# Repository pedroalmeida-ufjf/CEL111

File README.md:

# CEL111
Laboratório de Prototipagem Eletrônica

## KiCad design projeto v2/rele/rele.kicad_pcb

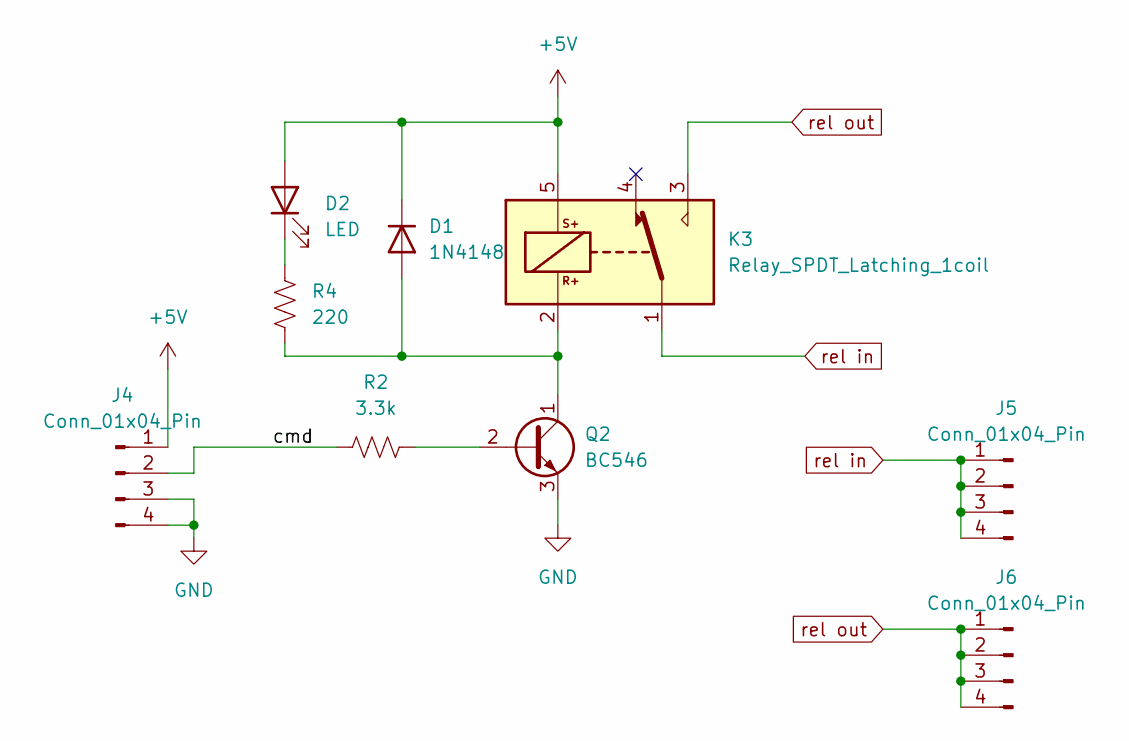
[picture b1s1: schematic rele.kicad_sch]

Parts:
D1: 1N4148; D_DO-35_SOD27_P7.62mm_Horizontal
D2: LED; LED_D3.0mm_Clear
J4, J5, J6: Conn_01x04_Pin; PinHeader_1x04_P2.54mm_Vertical
K3: Relay_SPDT_Latching_1coil; Relay_SPDT_SANYOU_SRD_Series_Form_C
Q2: BC546; TSOT-23
R2: 3.3k; R_0805_2012Metric
R4: 220; R_0805_2012Metric

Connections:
+5V: D1.1 (K), D2.2 (A), J4.1, K3.5
/cmd: J4.2, R2.2
GND: J4.3, J4.4, Q2.3 (E)
unnamed: D1.2 (A), K3.2, Q2.1 (C), R4.1
unnamed: D2.1 (K), R4.2
unnamed: Q2.2 (B), R2.1
rel in: J5.1, J5.2, J5.3, J5.4, K3.1
rel out: J6.1, J6.2, J6.3, J6.4, K3.3

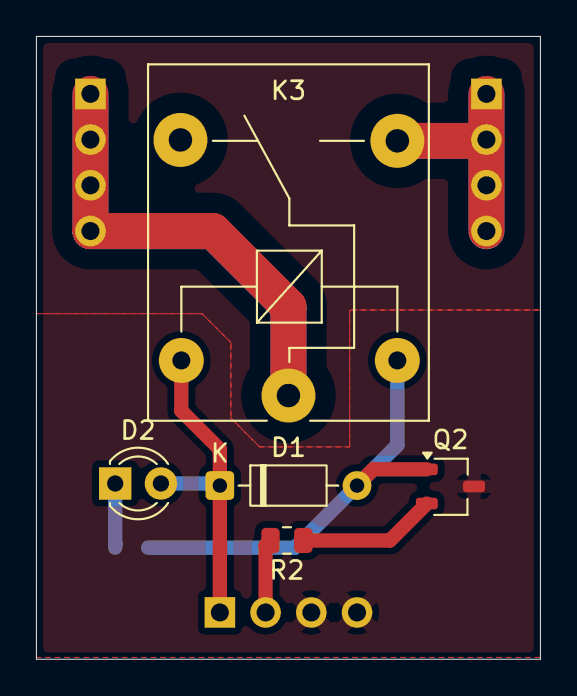
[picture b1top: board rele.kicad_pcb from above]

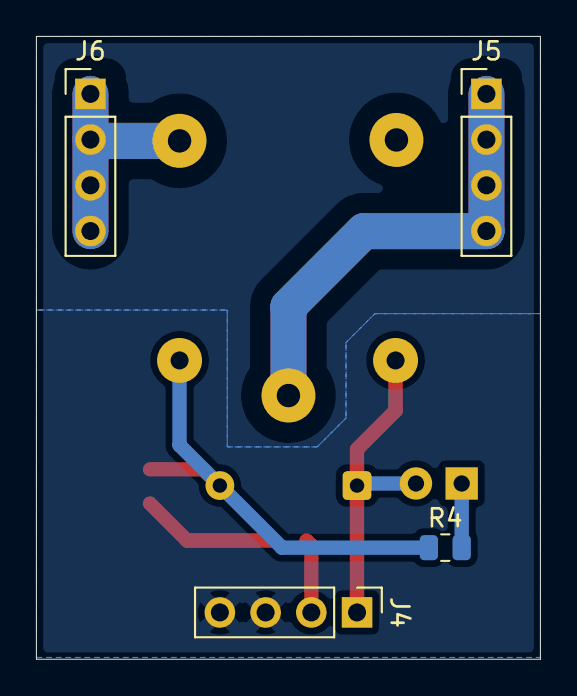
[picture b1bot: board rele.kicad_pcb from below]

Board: 2 copper layers, 28.0 x 34.6 mm, 9 parts (4 on the bottom side), 8 nets.

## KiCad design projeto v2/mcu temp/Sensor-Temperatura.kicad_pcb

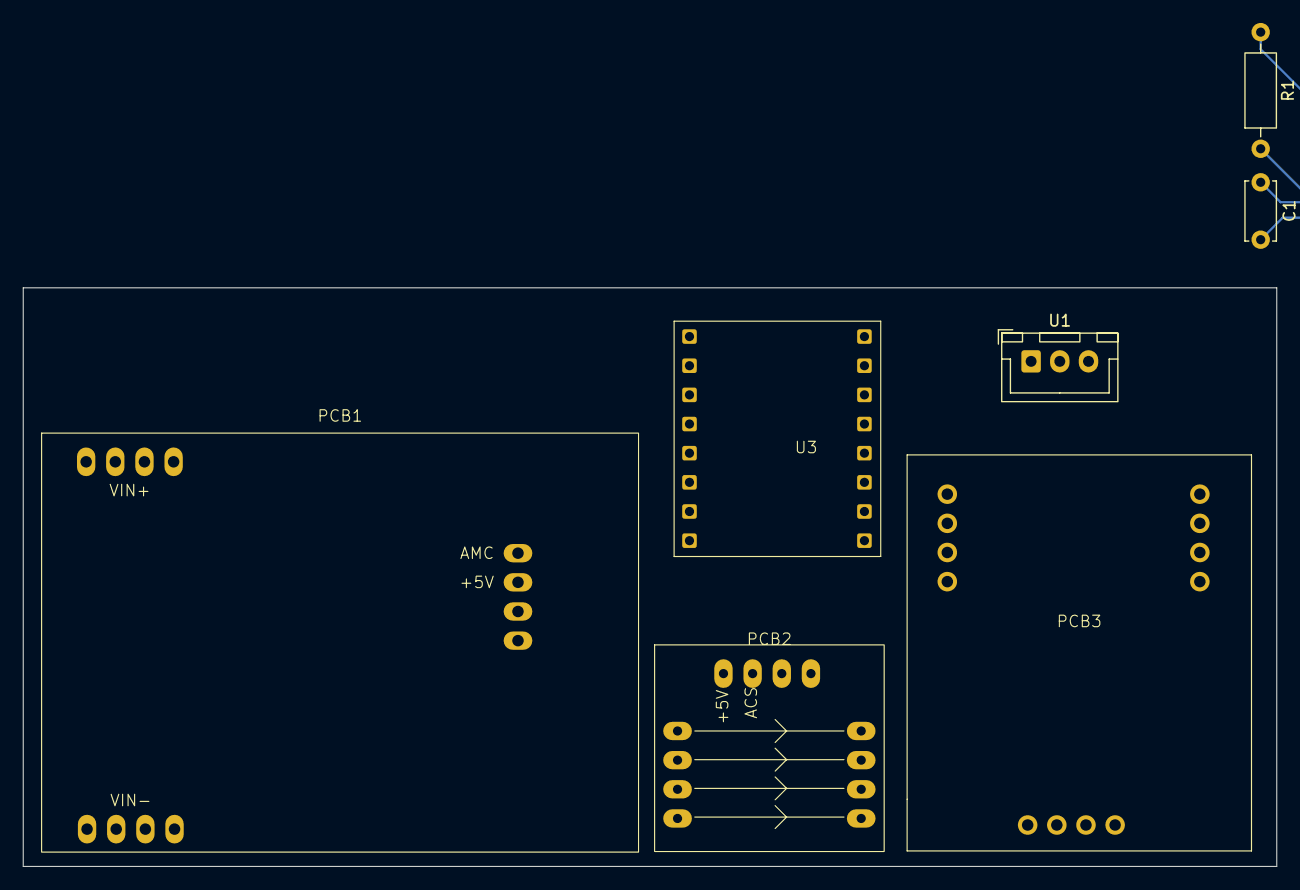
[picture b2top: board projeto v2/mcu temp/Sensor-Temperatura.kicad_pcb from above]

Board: 2 copper layers, 109.2 x 50.4 mm, 7 parts (0 on the bottom side), 9 nets.

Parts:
C1: 100nF; C_Disc_D5.0mm_W2.5mm_P5.00mm
PCB1: V-SENS
PCB2: I-SENS
PCB3: rele
R1: 4.7k; R_Axial_DIN0207_L6.3mm_D2.5mm_P10.16mm_Horizontal
U1: DS18B20; JST_XH_B3B-XH-A_1x03_P2.50mm_Vertical
U3: ESP32-C3_SUPERMINI_SMD; ESP32_C3_Supermini

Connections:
+3.3V: C1.1, R1.1, U1.3 (V_{DD}), U3.3.3 (3V3)
+5V: PCB1.10 (+5V), PCB2.9 (+5V), PCB3.10 (+5V), U3.5V
/TEMP_1WIRE: R1.2, U1.2 (DQ), U3.6 (GPIO6)
/VIN+: PCB1.1 (+VIN1), PCB1.2 (+VIN2), PCB1.3 (+VIN2), PCB1.4 (+VIN4), PCB2.1 (+IP), PCB2.2 (+IP), PCB2.3 (+IP), PCB2.4 (+IP)
/VIN-: PCB1.5 (-VIN1), PCB1.6 (-VIN2), PCB1.7 (-VIN2), PCB1.8 (-VIN4)
CMD: PCB3.9 (CMD), U3.3 (GPIO3)
GND: C1.2, PCB1.11 (GND), PCB1.12 (GND), PCB2.11 (GND), PCB2.12 (GND), PCB3.11 (GND), PCB3.12 (GND), U1.1 (GND), U3.G (GND)
unnamed: PCB3.5 (RLY-OUT), PCB3.6 (RLY-OUT), PCB3.7 (RLY-OUT), PCB3.8 (RLY-OUT)
unnamed: PCB2.5 (-IP), PCB2.6 (-IP), PCB2.7 (-IP), PCB2.8 (-IP), PCB3.1 (RLY-IN), PCB3.2 (RLY-IN), PCB3.3 (RLY-IN), PCB3.4 (RLY-IN)

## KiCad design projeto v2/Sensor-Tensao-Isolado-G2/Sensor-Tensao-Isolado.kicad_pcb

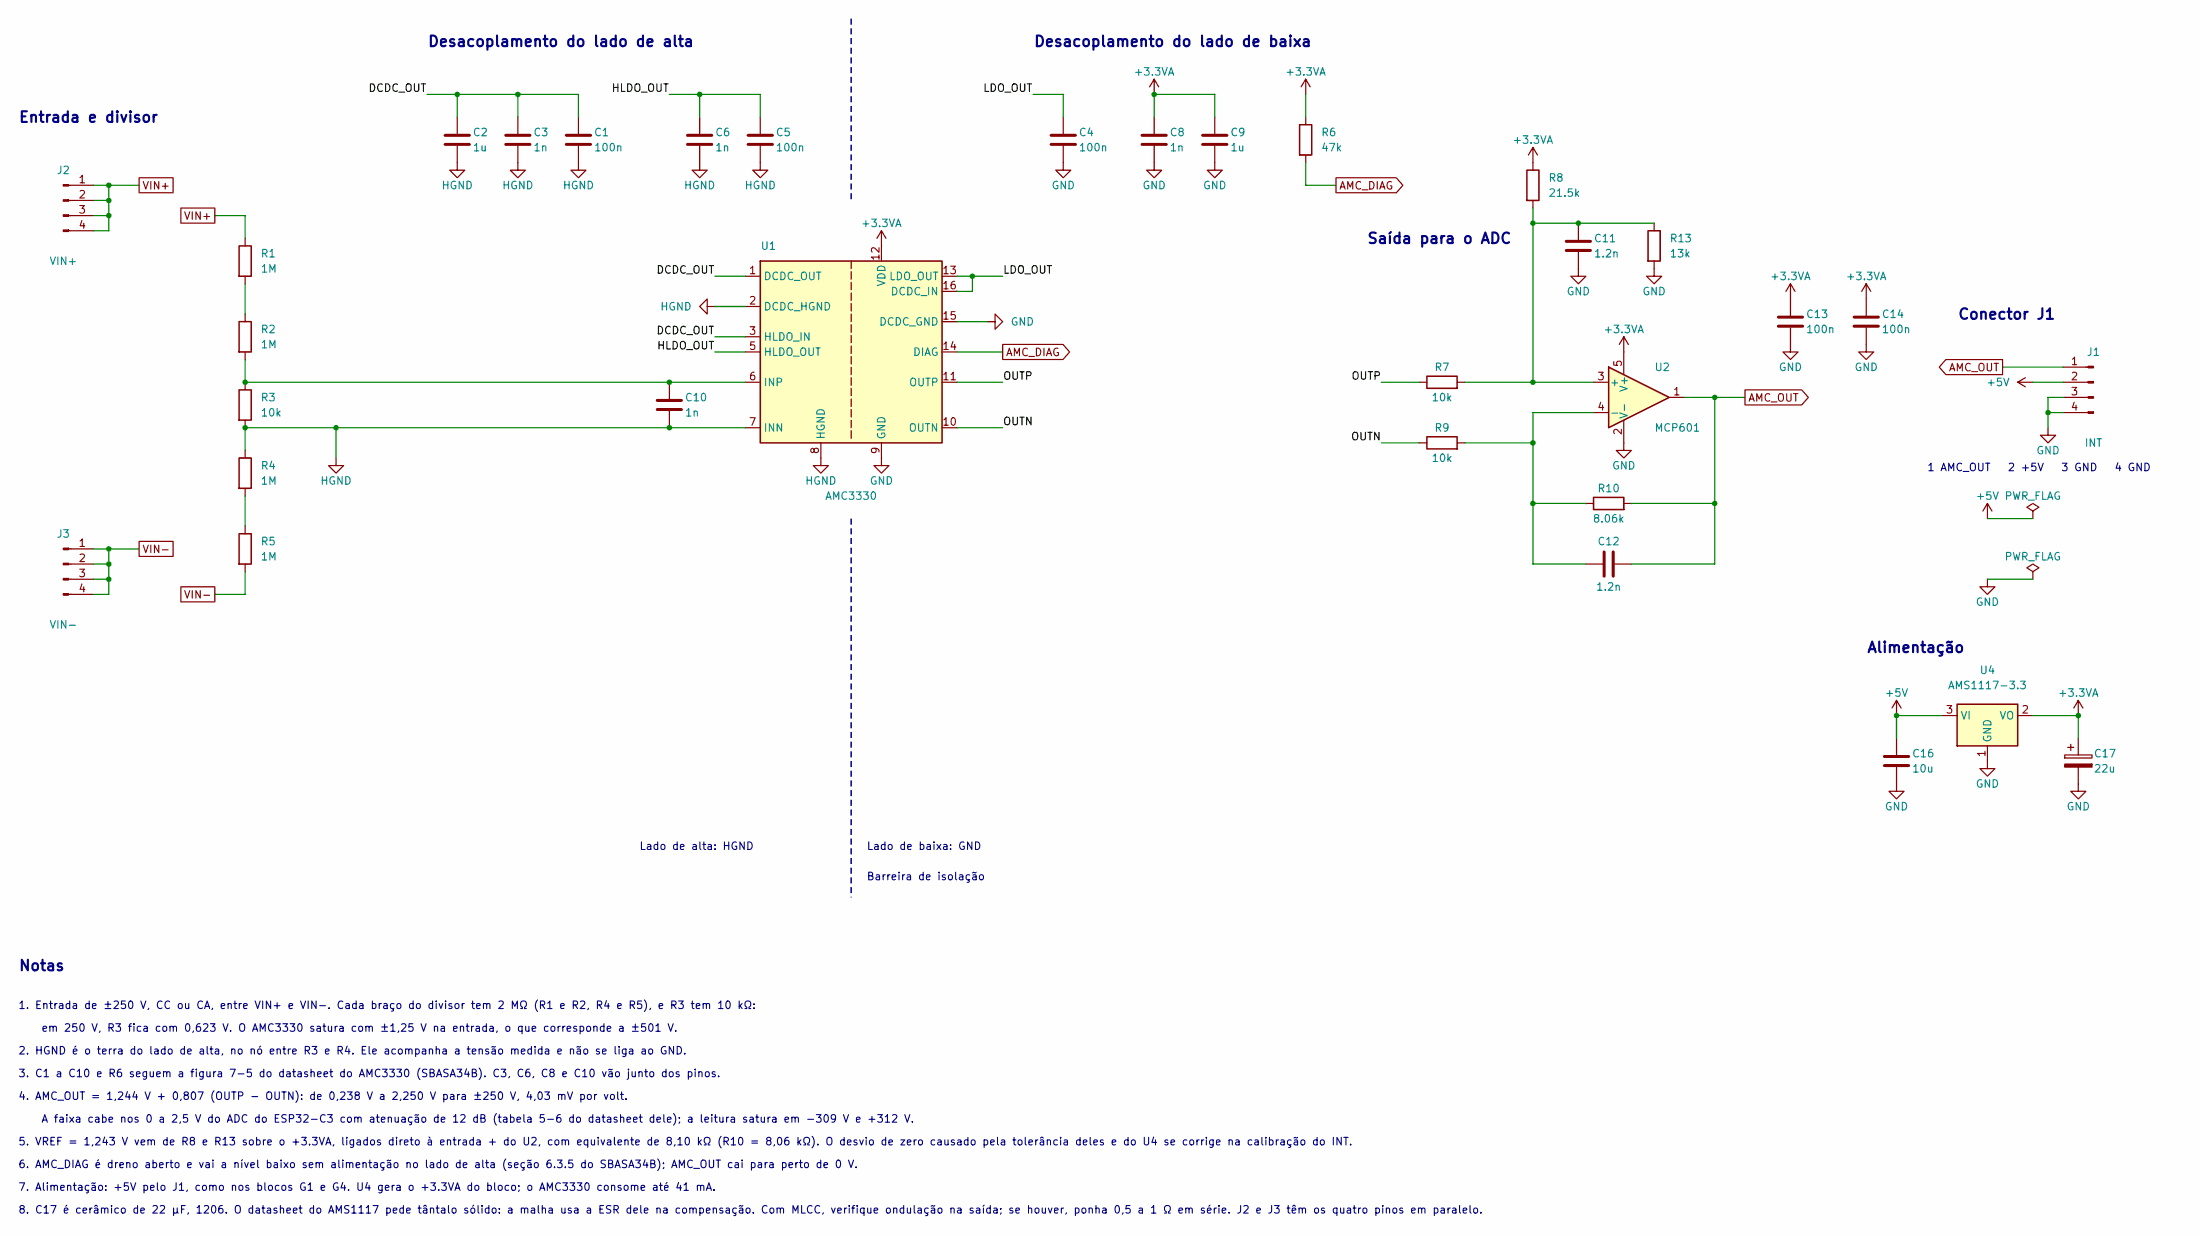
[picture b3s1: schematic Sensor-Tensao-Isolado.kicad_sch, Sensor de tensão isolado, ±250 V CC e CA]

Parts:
C1, C4, C5, C13, C14: 100n; C_1206_3216Metric_Pad1.33x1.80mm_HandSolder
C2, C9: 1u; C_1206_3216Metric_Pad1.33x1.80mm_HandSolder
C3, C6, C8, C10: 1n; C_1206_3216Metric_Pad1.33x1.80mm_HandSolder
C11, C12: 1.2n; C_1206_3216Metric_Pad1.33x1.80mm_HandSolder
C16: 10u; C_1206_3216Metric_Pad1.33x1.80mm_HandSolder
C17: 22u; C_1206_3216Metric_Pad1.33x1.80mm_HandSolder
J1: INT; PinHeader_1x04_P2.54mm_Vertical
J2: VIN+; PinHeader_1x04_P2.54mm_Vertical
J3: VIN-; PinHeader_1x04_P2.54mm_Vertical
R1, R2, R4, R5: 1M; R_1206_3216Metric_Pad1.30x1.75mm_HandSolder
R3, R7, R9: 10k; R_1206_3216Metric_Pad1.30x1.75mm_HandSolder
R6: 47k; R_1206_3216Metric_Pad1.30x1.75mm_HandSolder
R8: 21.5k; R_1206_3216Metric_Pad1.30x1.75mm_HandSolder
R10: 8.06k; R_1206_3216Metric_Pad1.30x1.75mm_HandSolder
R13: 13k; R_1206_3216Metric_Pad1.30x1.75mm_HandSolder
U1: AMC3330; SOIC-16W_7.5x10.3mm_P1.27mm
U2: MCP601; SOT-23-5
U4: AMS1117-3.3; SOT-223-3_TabPin2

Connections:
+3.3VA: C8.1, C9.1, C13.1, C14.1, C17.1, R6.1, R8.1, U1.12 (VDD), U2.5 (V+), U4.2 (VO)
+5V: C16.1, J1.2, U4.3 (VI)
/DCDC_OUT: C1.1, C2.1, C3.1, U1.1 (DCDC_OUT), U1.3 (HLDO_IN)
/HLDO_OUT: C5.1, C6.1, U1.5 (HLDO_OUT)
/LDO_OUT: C4.1, U1.13 (LDO_OUT), U1.16 (DCDC_IN)
/OUTN: R9.1, U1.10 (OUTN)
/OUTP: R7.1, U1.11 (OUTP)
AMC_DIAG: R6.2, U1.14 (DIAG)
AMC_OUT: C12.2, J1.1, R10.2, U2.1
GND: C4.2, C8.2, C9.2, C11.2, C13.2, C14.2, C16.2, C17.2, J1.3, J1.4, R13.2, U1.9 (GND), U1.15 (DCDC_GND), U2.2 (V-), U4.1 (GND)
HGND: C1.2, C2.2, C3.2, C5.2, C6.2, C10.2, R3.2, R4.1, U1.2 (DCDC_HGND), U1.7 (INN), U1.8 (HGND)
unnamed: R1.2, R2.1
unnamed: R4.2, R5.1
unnamed: C10.1, R2.2, R3.1, U1.6 (INP)
unnamed: C11.1, R7.2, R8.2, R13.1, U2.3 (+)
unnamed: C12.1, R9.2, R10.1, U2.4 (-)
VIN+: J2.1, J2.2, J2.3, J2.4, R1.1
VIN-: J3.1, J3.2, J3.3, J3.4, R5.2

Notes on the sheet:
8. C17 é cerâmico de 22 µF, 1206. O datasheet do AMS1117 pede tântalo sólido: a malha usa a ESR dele na compensação. Com MLCC, verifique ondulação na saída; se houver, ponha 0,5 a 1 Ω em série. J2 e J3 têm os quatro pinos em paralelo.
em 250 V, R3 fica com 0,623 V. O AMC3330 satura com ±1,25 V na entrada, o que corresponde a ±501 V.
Lado de baixa: GND
1 AMC_OUT 2 +5V 3 GND 4 GND
Barreira de isolação
7. Alimentação: +5V pelo J1, como nos blocos G1 e G4. U4 gera o +3.3VA do bloco; o AMC3330 consome até 41 mA.
Lado de alta: HGND
4. AMC_OUT = 1,244 V + 0,807 (OUTP - OUTN): de 0,238 V a 2,250 V para ±250 V, 4,03 mV por volt.
Notas
1. Entrada de ±250 V, CC ou CA, entre VIN+ e VIN-. Cada braço do divisor tem 2 MΩ (R1 e R2, R4 e R5), e R3 tem 10 kΩ:
Entrada e divisor
6. AMC_DIAG é dreno aberto e vai a nível baixo sem alimentação no lado de alta (seção 6.3.5 do SBASA34B); AMC_OUT cai para perto de 0 V.
3. C1 a C10 e R6 seguem a figura 7-5 do datasheet do AMC3330 (SBASA34B). C3, C6, C8 e C10 vão junto dos pinos.
A faixa cabe nos 0 a 2,5 V do ADC do ESP32-C3 com atenuação de 12 dB (tabela 5-6 do datasheet dele); a leitura satura em -309 V e +312 V.
2. HGND é o terra do lado de alta, no nó entre R3 e R4. Ele acompanha a tensão medida e não se liga ao GND.
5. VREF = 1,243 V vem de R8 e R13 sobre o +3.3VA, ligados direto à entrada + do U2, com equivalente de 8,10 kΩ (R10 = 8,06 kΩ). O desvio de zero causado pela tolerância deles e do U4 se corrige na calibração do INT.
Conector J1
Saída para o ADC
Alimentação
Desacoplamento do lado de alta
Desacoplamento do lado de baixa

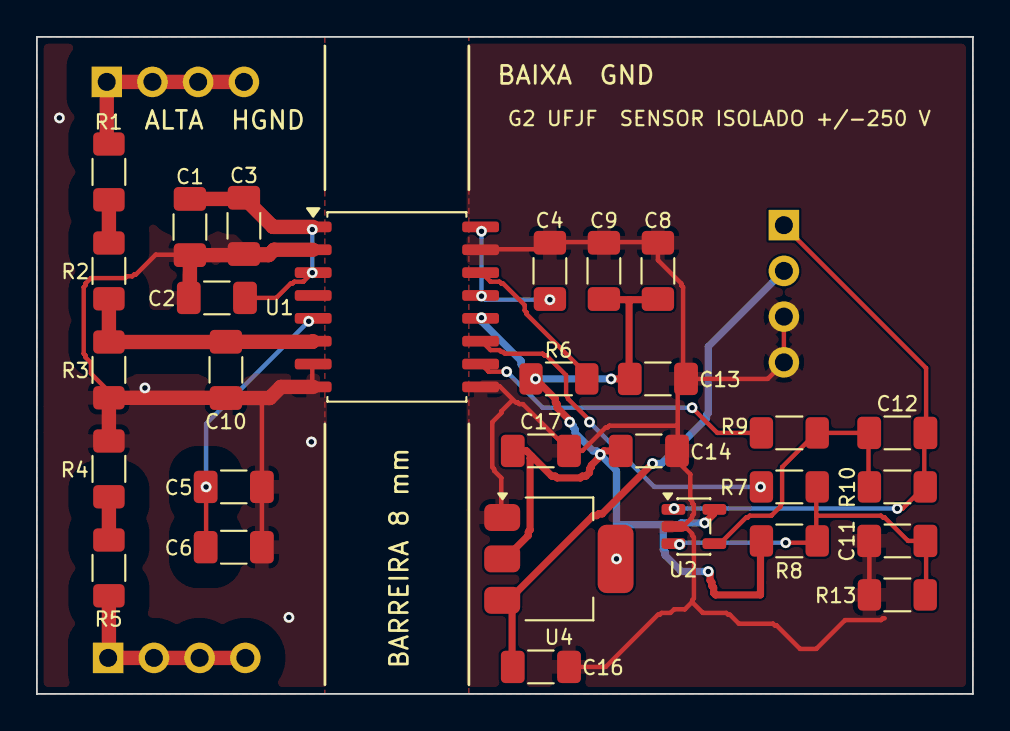
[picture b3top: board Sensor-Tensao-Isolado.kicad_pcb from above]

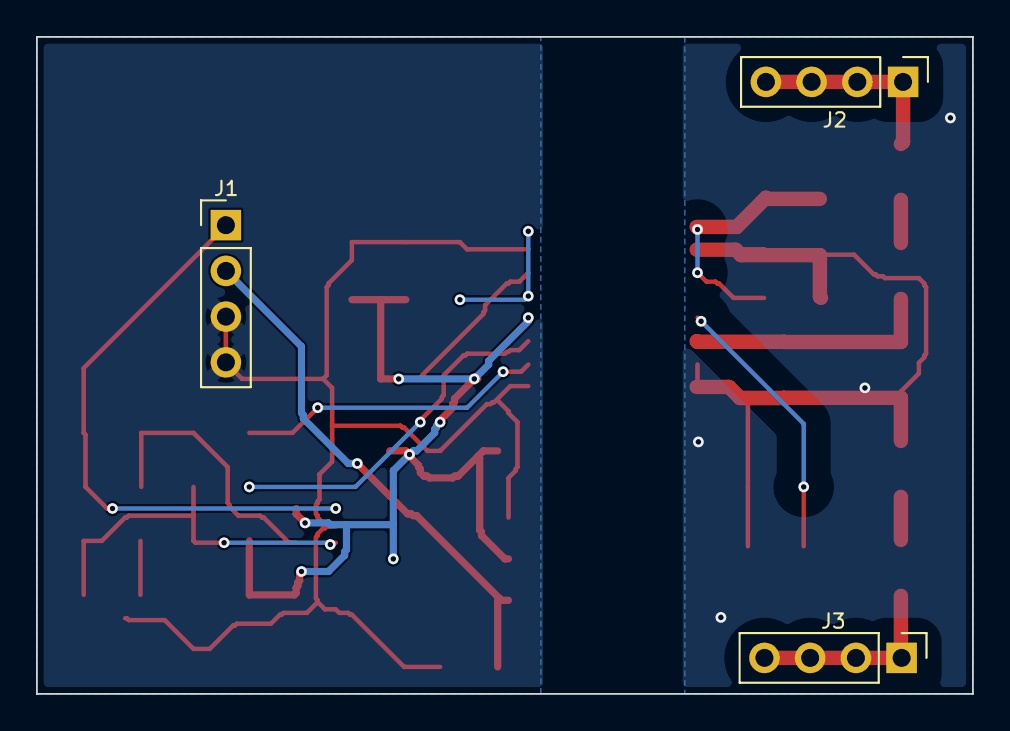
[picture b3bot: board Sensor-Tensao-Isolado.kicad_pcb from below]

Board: 2 copper layers, 52.0 x 36.5 mm, 32 parts (3 on the bottom side), 18 nets.

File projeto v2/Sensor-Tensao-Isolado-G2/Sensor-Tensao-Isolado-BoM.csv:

"Referência","Valor","Especificação","Footprint","Qtd"
"C1,C4,C13,C14","100n","X7R, 50 V, 1206","Capacitor_SMD:C_1206_3216Metric_Pad1.33x1.80mm_HandSolder","4"
"C2,C9","1u","X7R, 25 V, 1206","Capacitor_SMD:C_1206_3216Metric_Pad1.33x1.80mm_HandSolder","2"
"C3,C6,C8","1n","X7R, 50 V, 1206","Capacitor_SMD:C_1206_3216Metric_Pad1.33x1.80mm_HandSolder","3"
"C5","100n","C0G, 50 V, 1206","Capacitor_SMD:C_1206_3216Metric_Pad1.33x1.80mm_HandSolder","1"
"C10","1n","C0G, 50 V, 1206","Capacitor_SMD:C_1206_3216Metric_Pad1.33x1.80mm_HandSolder","1"
"C11,C12","1.2n","C0G, 50 V, 1206","Capacitor_SMD:C_1206_3216Metric_Pad1.33x1.80mm_HandSolder","2"
"C16","10u","X7R, 25 V, 1206","Capacitor_SMD:C_1206_3216Metric_Pad1.33x1.80mm_HandSolder","1"
"C17","22u","X5R, 16 V, 1206","Capacitor_SMD:C_1206_3216Metric_Pad1.33x1.80mm_HandSolder","1"
"J1","INT","barra de pinos 1x4, passo 2,54 mm","Connector_PinHeader_2.54mm:PinHeader_1x04_P2.54mm_Vertical","1"
"J2","VIN+","barra de pinos 1x4, passo 2,54 mm","Connector_PinHeader_2.54mm:PinHeader_1x04_P2.54mm_Vertical","1"
"J3","VIN-","barra de pinos 1x4, passo 2,54 mm","Connector_PinHeader_2.54mm:PinHeader_1x04_P2.54mm_Vertical","1"
"R1,R2,R4,R5","1M","1 %, 1206, tensão de trabalho de 200 V ou mais","Resistor_SMD:R_1206_3216Metric_Pad1.30x1.75mm_HandSolder","4"
"R3,R7,R9","10k","1 %, 1206","Resistor_SMD:R_1206_3216Metric_Pad1.30x1.75mm_HandSolder","3"
"R6","47k","1 %, 1206","Resistor_SMD:R_1206_3216Metric_Pad1.30x1.75mm_HandSolder","1"
"R8","21.5k","1 %, 1206","Resistor_SMD:R_1206_3216Metric_Pad1.30x1.75mm_HandSolder","1"
"R10","8.06k","1 %, 1206","Resistor_SMD:R_1206_3216Metric_Pad1.30x1.75mm_HandSolder","1"
"R13","13k","1 %, 1206","Resistor_SMD:R_1206_3216Metric_Pad1.30x1.75mm_HandSolder","1"
"U1","AMC3330","AMC3330DWE ou AMC3330DWER","Package_SO:SOIC-16W_7.5x10.3mm_P1.27mm","1"
"U2","MCP601","TLV6001IDBVR","Package_TO_SOT_SMD:SOT-23-5","1"
"U4","AMS1117-3.3","AMS1117-3.3, SOT-223","Package_TO_SOT_SMD:SOT-223-3_TabPin2","1"

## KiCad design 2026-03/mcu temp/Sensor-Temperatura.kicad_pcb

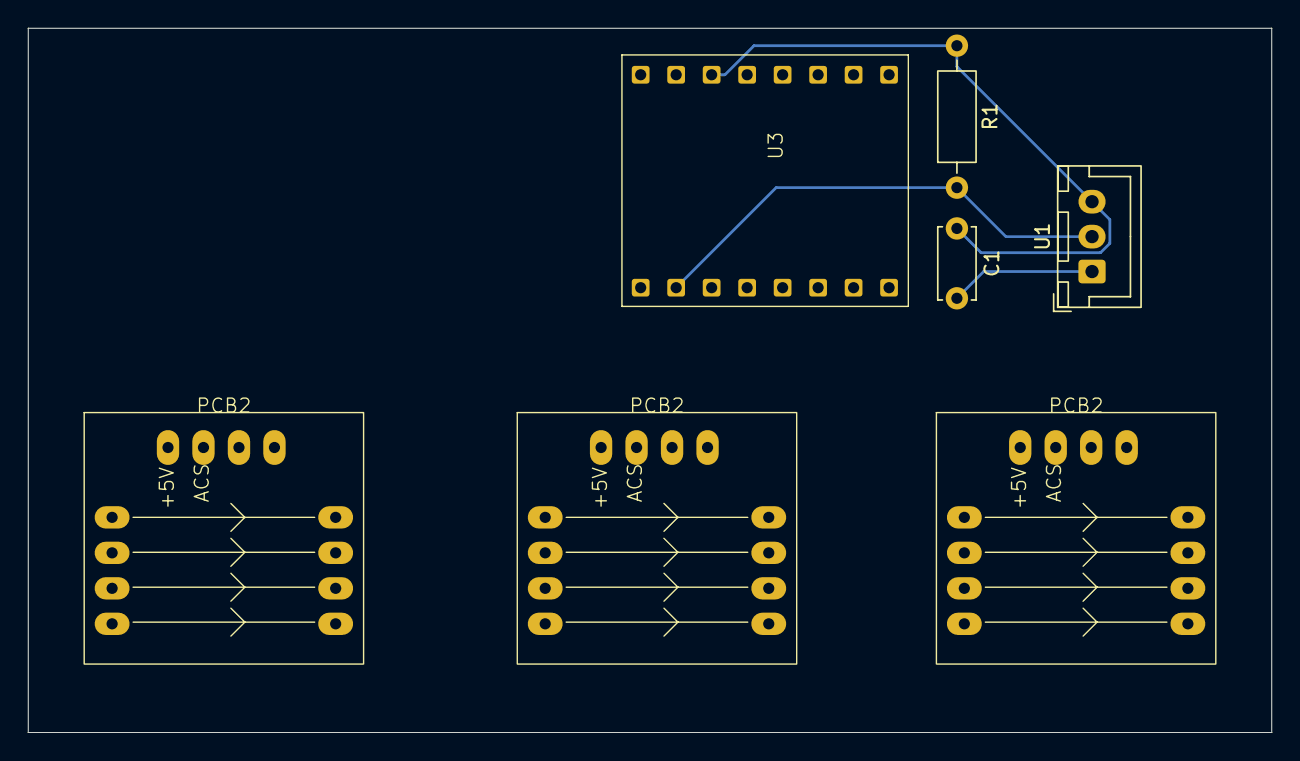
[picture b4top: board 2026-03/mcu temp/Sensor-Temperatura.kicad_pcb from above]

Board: 2 copper layers, 89.0 x 50.4 mm, 7 parts (0 on the bottom side), 6 nets.

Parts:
C1: 100nF; C_Disc_D5.0mm_W2.5mm_P5.00mm
PCB2, PCB2#2, PCB2#3: I-SENS
R1: 4.7k; R_Axial_DIN0207_L6.3mm_D2.5mm_P10.16mm_Horizontal
U1: DS18B20; JST_XH_B3B-XH-A_1x03_P2.50mm_Vertical
U3: ESP32-C3_SUPERMINI_SMD; ESP32_C3_Supermini

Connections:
+3.3V: C1.1, R1.1, U1.3 (V_{DD}), U3.3.3 (3V3)
+5V: PCB2#2.9 (+5V), U3.5V
/TEMP_1WIRE: R1.2, U1.2 (DQ), U3.6 (GPIO6)
/VIN+: PCB2#2.1 (+IP), PCB2#2.2 (+IP), PCB2#2.3 (+IP), PCB2#2.4 (+IP)
GND: C1.2, PCB2#2.11 (GND), PCB2#2.12 (GND), U1.1 (GND), U3.G (GND)
unnamed: PCB2#2.5 (-IP), PCB2#2.6 (-IP), PCB2#2.7 (-IP), PCB2#2.8 (-IP)

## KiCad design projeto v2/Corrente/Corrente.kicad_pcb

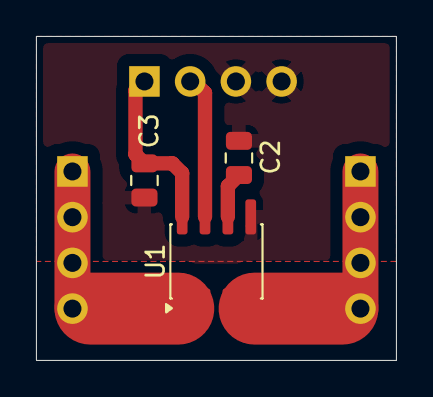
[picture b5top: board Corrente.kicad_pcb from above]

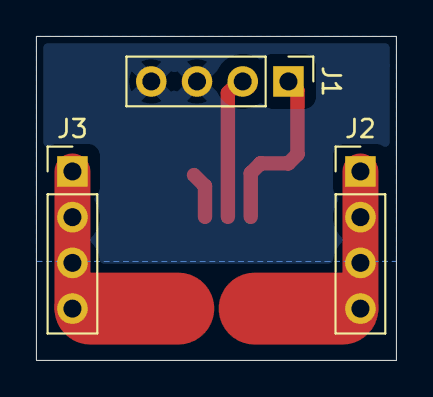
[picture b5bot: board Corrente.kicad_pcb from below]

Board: 2 copper layers, 20.0 x 18.0 mm, 6 parts (3 on the bottom side), 6 nets.

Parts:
C2, C3: 0.1u; C_0805_2012Metric
J1, J2, J3: Conn_01x04_Pin; PinHeader_1x04_P2.54mm_Vertical
U1: ACS712xLCTR-05B; SOIC-8_3.9x4.9mm_P1.27mm

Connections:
+5V: C3.1, J1.1, U1.8 (VCC)
/FILTER: C2.1, U1.6 (FILTER)
/IP+: J2.1, J2.2, J2.3, J2.4, U1.1 (IP+), U1.2 (IP+)
/IP-: J3.1, J3.2, J3.3, J3.4, U1.3 (IP-), U1.4 (IP-)
ACS_OUT: J1.2, U1.7 (VIOUT)
GND: C2.2, C3.2, J1.3, J1.4, U1.5 (GND)
